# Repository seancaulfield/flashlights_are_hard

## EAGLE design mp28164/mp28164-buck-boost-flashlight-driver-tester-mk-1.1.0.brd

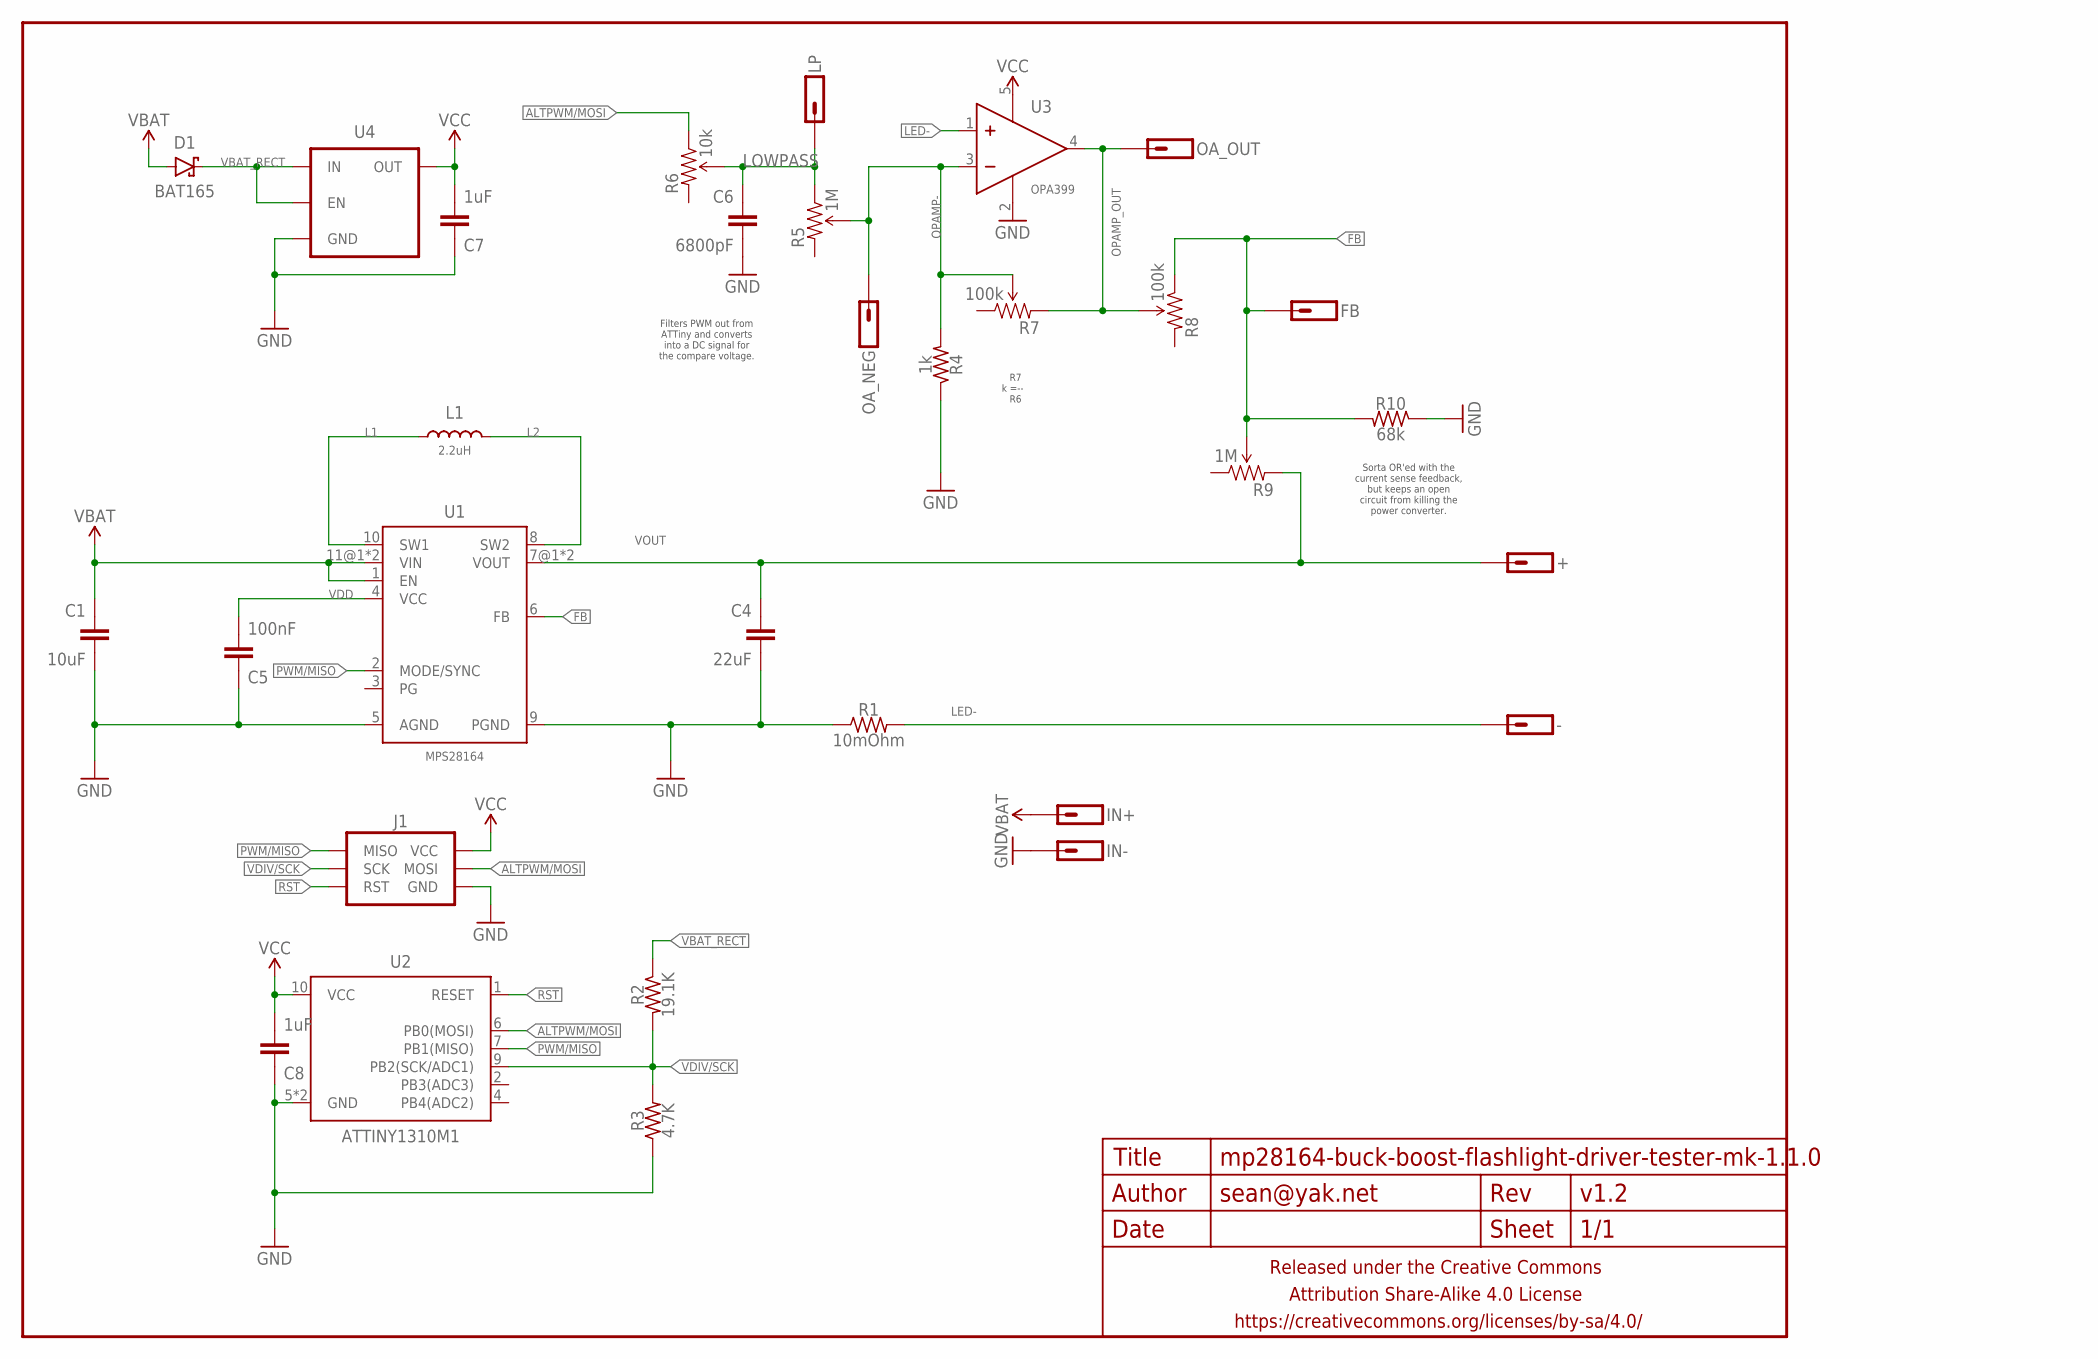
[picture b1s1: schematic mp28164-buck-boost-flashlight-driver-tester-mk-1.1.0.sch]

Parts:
+: M01PTH-1MM-CIR-NS; 1X01-1MM-CIR-NS
-: M01PTH-1MM-CIR-NS; 1X01-1MM-CIR-NS
C1: 10uF; C1206
C4: 22uF; C1206
C5: 100nF; C0402
C6: 6800pF; C0402
C7, C8: 1uF; C0402
D1: BAT165; SOD323-SCHOTTKY
FB: M01SMD-1MM-DIA-NS; 1X01-SMD-1MM-DIA-NS
FRAME1: FRAME-LETTERNO_PACKAGE; DUMMY
IN+: M01PTH-1MM-CIR-NS; 1X01-1MM-CIR-NS
IN-: M01PTH-1MM-CIR-NS; 1X01-1MM-CIR-NS
J1: AVR_SPI_PRG_6PTH; 2X3
L1: 2.2uH; XAL7070
LP: M01SMD-1MM-DIA-NS; 1X01-SMD-1MM-DIA-NS
OA_NEG: M01SMD-1MM-DIA-NS; 1X01-SMD-1MM-DIA-NS
OA_OUT: M01SMD-1MM-DIA-NS; 1X01-SMD-1MM-DIA-NS
R1: 10mOhm; R1206
R2: 19.1K; R0402
R3: 4.7K; R0402
R4: 1k; R0402
R5, R9: 1M; EVM3Y-LESS
R6: 10k; EVM3Y-LESS
R7, R8: 100k; EVM3Y-LESS
R10: 68k; R0402
U1: MPS28164
U2: ATTINY1310M1; QFN10(2X5)
U3: OPA399; SC70
U4: V_REG_ENTLV700; SC70

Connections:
ALTPWM/MOSI: J1.4 (MOSI), R6.A (CCW), U2.6 (PB0(MOSI))
FB: FB.P$1, R8.A (CCW), R9.S (WIPER), R10.2, U1.6 (FB)
GND: C1.2, C4.2, C5.1, C6.2, C7.1, C8.1, IN-.1, J1.6 (GND), R1.1, R3.1, R4.1, R10.1, U1.5 (AGND), U1.9 (PGND), U2.5 (GND), U2.PAD (GND), U3.2 (V-), U4.2 (GND)
L1: L1.P$1 (1), U1.10 (SW1)
L2: L1.P$2 (2), U1.8 (SW2)
LED-: -.1, R1.2, U3.1 (IN+)
LOWPASS: C6.1, LP.P$1, R5.A (CCW), R6.S (WIPER)
OPAMP-: OA_NEG.P$1, R4.2, R5.S (WIPER), R7.S (WIPER), U3.3 (IN-)
OPAMP_OUT: OA_OUT.P$1, R7.E (CW), R8.S (WIPER), U3.4 (OUT)
PWM/MISO: J1.1 (MISO), U1.2 (MODE/SYNC), U2.7 (PB1(MISO))
RST: J1.5 (RST), U2.1 (RESET)
VBAT: C1.1, D1.A, IN+.1, U1.1 (EN), U1.11@1 (VIN), U1.11@2 (VIN)
VBAT_RECT: D1.C, R2.1, U4.1 (IN), U4.3 (EN)
VCC: C7.2, C8.2, J1.2 (VCC), U2.10 (VCC), U3.5 (V+), U4.5 (OUT)
VDD: C5.2, U1.4 (VCC)
VDIV/SCK: J1.3 (SCK), R2.2, R3.2, U2.9 (PB2(SCK/ADC1))
VOUT: +.1, C4.1, R9.E (CW), U1.7@1 (VOUT), U1.7@2 (VOUT)

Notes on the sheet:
Filters PWM out from ATTiny and converts into a DC signal for the compare voltage.
R7 k =-- R6
Sorta OR'ed with the current sense feedback, but keeps an open circuit from killing the power converter.

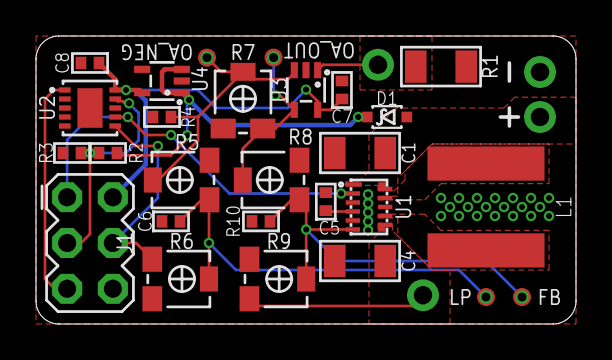
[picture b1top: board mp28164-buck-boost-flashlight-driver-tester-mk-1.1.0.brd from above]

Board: 2 copper layers, 30.0 x 16.0 mm, 32 parts (0 on the bottom side), 17 nets.

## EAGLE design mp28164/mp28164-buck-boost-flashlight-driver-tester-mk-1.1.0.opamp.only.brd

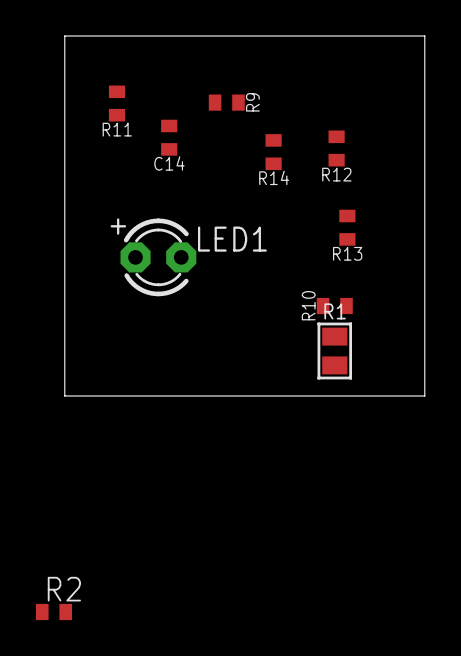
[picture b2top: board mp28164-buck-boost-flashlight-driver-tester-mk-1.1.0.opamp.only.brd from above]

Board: 2 copper layers, 20.0 x 20.0 mm, 10 parts (0 on the bottom side), 7 nets, no tracks yet.

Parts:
C14: 0.000001; C0402
LED1: LED3MM
R1: .01; R0805-TIGHTER
R2: 91000; R0402
R9, R10: 10000; R0402
R11: 150000; R0402
R12: 47000; R0402
R13: 750000; R0402
R14: 360000; R0402

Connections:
GND: C14.2, R1.1, R10.2, R11.1
LED-: LED1.K, R1.2
LOWPASS: C14.1, R9.1, R14.2
MIX1: R11.2, R12.1, R13.1
OPAMP-: R2.2, R10.1
OPAMP_OUT: R2.1, R12.2
VCC: LED1.A, R13.2

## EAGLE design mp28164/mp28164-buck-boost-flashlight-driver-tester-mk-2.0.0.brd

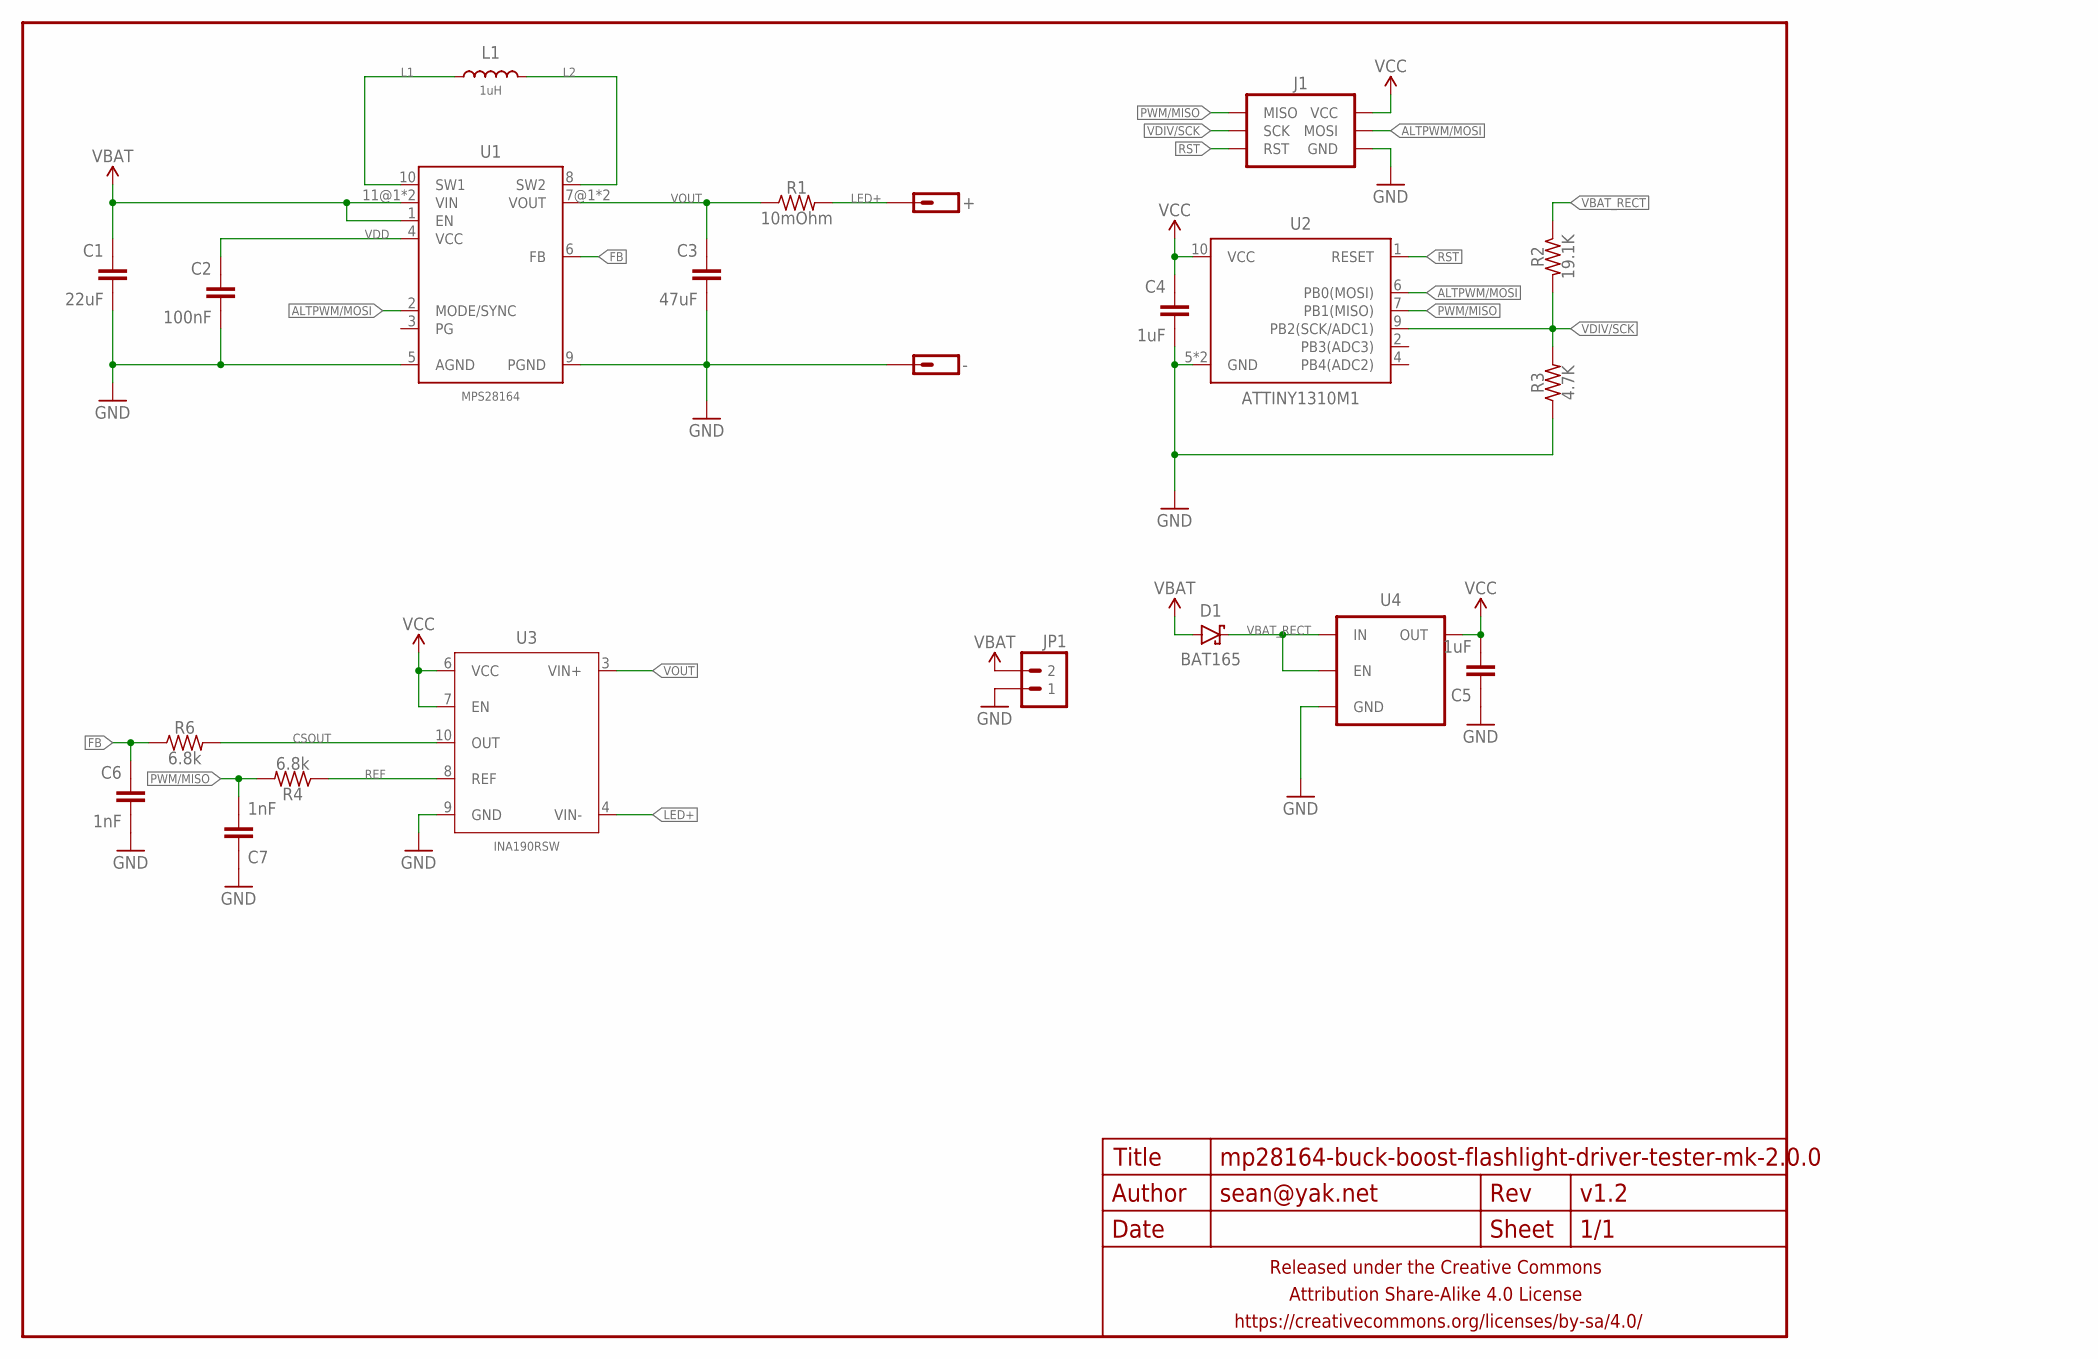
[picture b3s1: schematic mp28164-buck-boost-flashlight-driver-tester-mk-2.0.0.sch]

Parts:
+: M01PTH-1.2MM-NS; 1X01-1.2MM-NS
-: M01PTH-1.2MM-NS; 1X01-1.2MM-NS
C1: 22uF; C1206
C2: 100nF; C0402
C3: 47uF; C1206
C4, C5: 1uF; C0402
C6, C7: 1nF; C0402
D1: BAT165; SOD323-SCHOTTKY
FRAME1: FRAME-LETTERNO_PACKAGE; DUMMY
J1: AVR_SPI_PRG_6PTH; 2X3
JP1: M02PTH; 1X02
L1: 1uH; XAL60XX
R1: 10mOhm; R1206
R2: 19.1K; R0402
R3: 4.7K; R0402
R4, R6: 6.8k; R0402
U1: MPS28164
U2: ATTINY1310M1; QFN10(2X5)
U3: INA190RSW; UQFN-10
U4: V_REG_ENTLV700; SC70

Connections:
ALTPWM/MOSI: J1.4 (MOSI), U1.2 (MODE/SYNC), U2.6 (PB0(MOSI))
CSOUT: R6.2, U3.10 (OUT)
FB: C6.1, R6.1, U1.6 (FB)
GND: -.P$1, C1.2, C2.2, C3.2, C4.2, C5.1, C6.2, C7.1, J1.6 (GND), JP1.1, R3.1, U1.5 (AGND), U1.9 (PGND), U2.5 (GND), U2.PAD (GND), U3.9 (GND), U4.2 (GND)
L1: L1.P$1 (1), U1.10 (SW1)
L2: L1.P$2 (2), U1.8 (SW2)
LED+: +.P$1, R1.2, U3.4 (VIN-)
PWM/MISO: C7.2, J1.1 (MISO), R4.2, U2.7 (PB1(MISO))
REF: R4.1, U3.8 (REF)
RST: J1.5 (RST), U2.1 (RESET)
VBAT: C1.1, D1.A, JP1.2, U1.1 (EN), U1.11@1 (VIN), U1.11@2 (VIN)
VBAT_RECT: D1.C, R2.1, U4.1 (IN), U4.3 (EN)
VCC: C4.1, C5.2, J1.2 (VCC), U2.10 (VCC), U3.6 (VCC), U3.7 (EN), U4.5 (OUT)
VDD: C2.1, U1.4 (VCC)
VDIV/SCK: J1.3 (SCK), R2.2, R3.2, U2.9 (PB2(SCK/ADC1))
VOUT: C3.1, R1.1, U1.7@1 (VOUT), U1.7@2 (VOUT), U3.3 (VIN+)

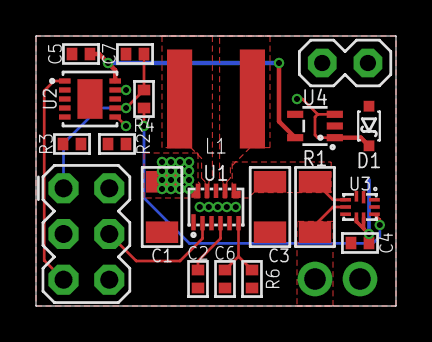
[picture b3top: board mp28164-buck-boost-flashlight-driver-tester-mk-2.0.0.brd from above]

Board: 2 copper layers, 20.0 x 15.0 mm, 23 parts (0 on the bottom side), 16 nets.

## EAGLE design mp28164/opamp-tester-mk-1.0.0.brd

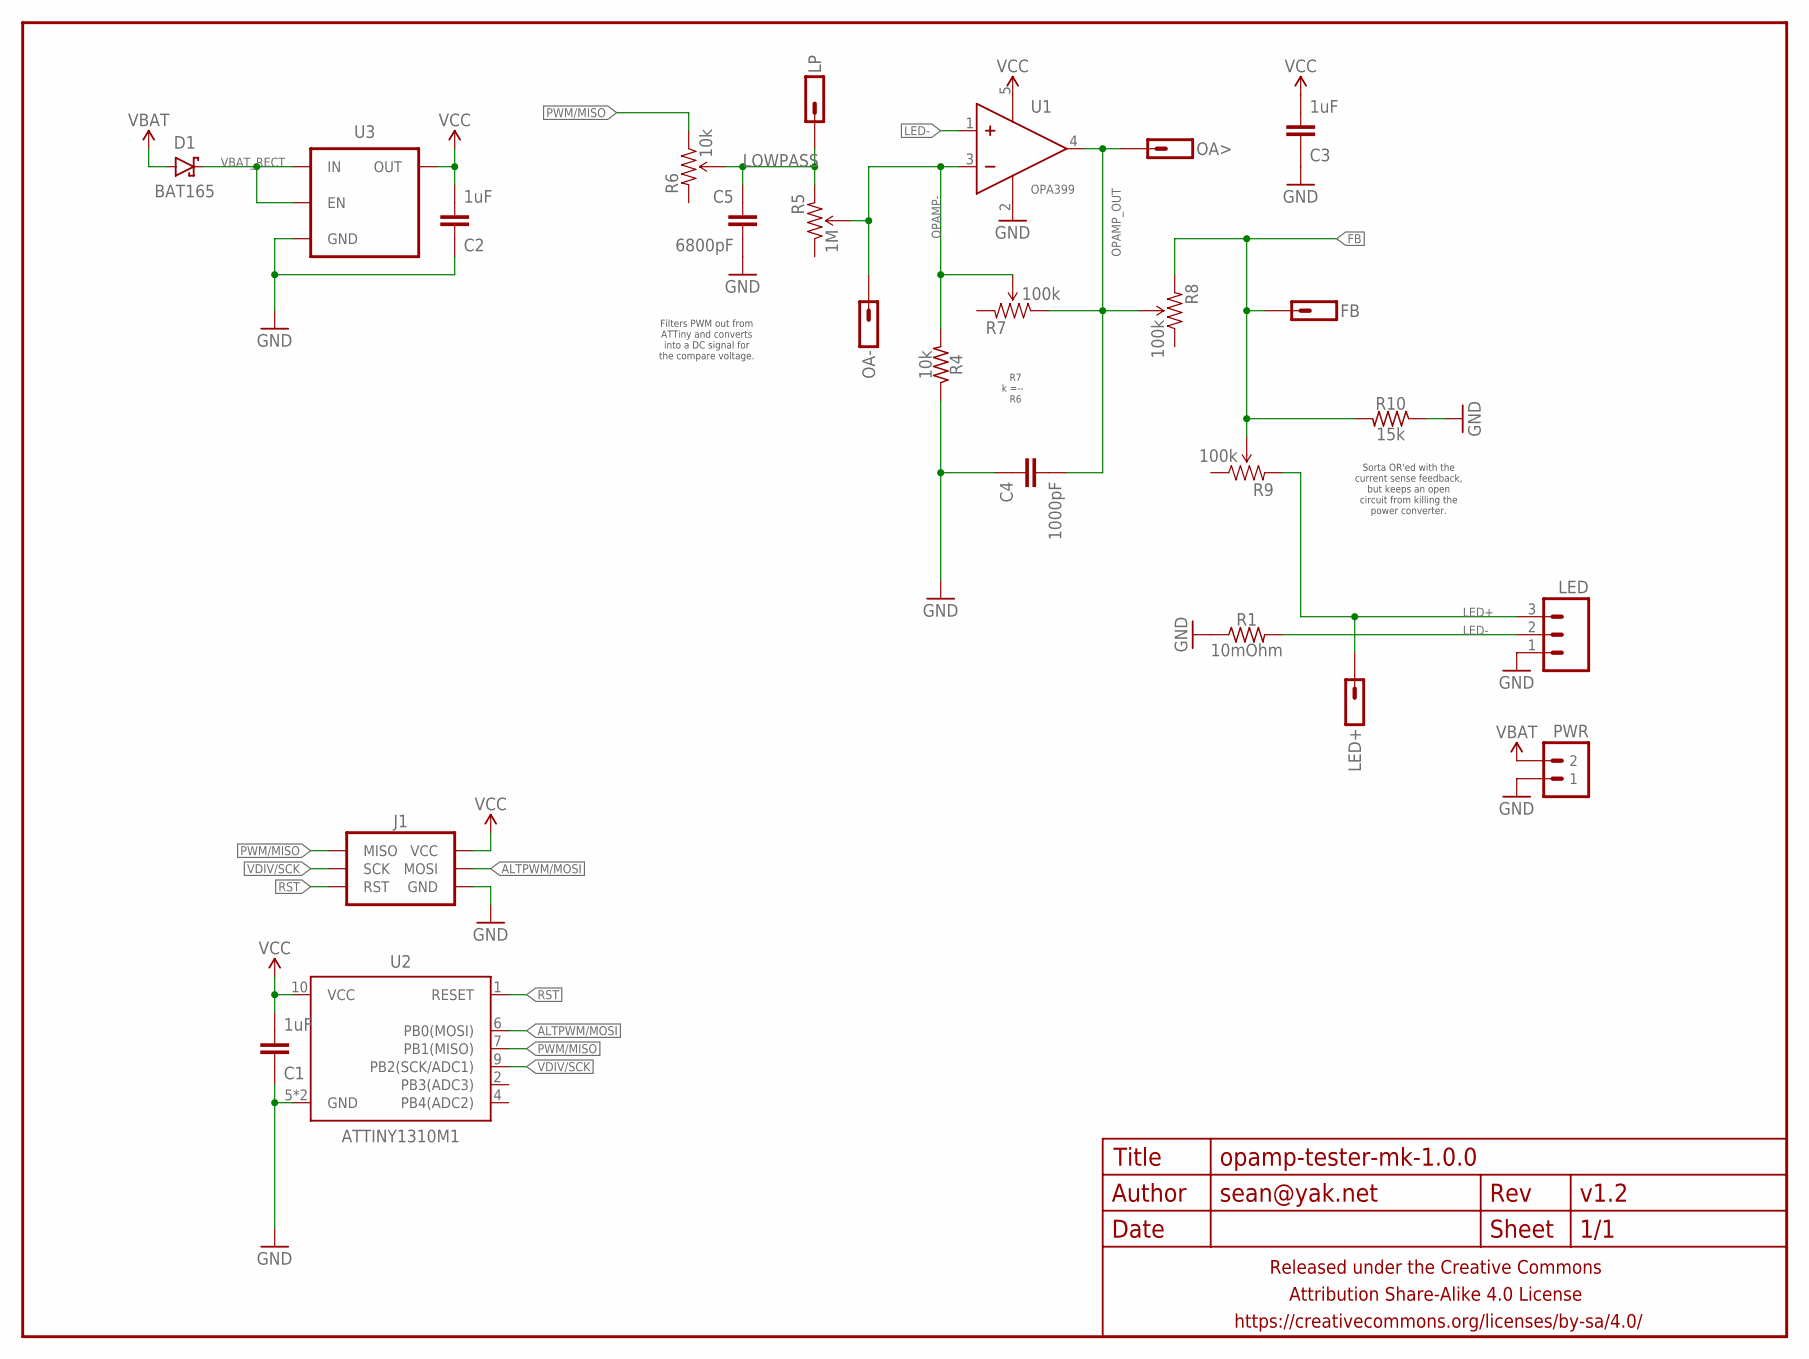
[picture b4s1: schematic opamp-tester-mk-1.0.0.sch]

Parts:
C1, C2, C3: 1uF; C0402
C4: 1000pF; C0402
C5: 6800pF; C0402
D1: BAT165; SOD323-SCHOTTKY
FB: M01PTH-0.7MM-CIR; 1X01-0.7MM-CIR
FRAME1: FRAME-LETTERNO_PACKAGE; DUMMY
J1: AVR_SPI_PRG_6SMD_TEST_POINTS; 2X3_SMD_TEST_POINTS
LED: M03SCREW; SCREWTERMINAL-3.5MM-3
LED+: M01PTH-0.7MM-CIR; 1X01-0.7MM-CIR
LP: M01PTH-0.7MM-CIR; 1X01-0.7MM-CIR
OA-: M01PTH-0.7MM-CIR; 1X01-0.7MM-CIR
OA>: M01PTH-0.7MM-CIR; 1X01-0.7MM-CIR
PWR: M02PTH-2MM; 1X02-2MM-PTH
R1: 10mOhm; R1206
R4: 10k; R0402
R5: 1M; EVM3Y-LESS
R6: 10k; EVM3Y-LESS
R7, R8, R9: 100k; EVM3Y-LESS
R10: 15k; R0402
U1: OPA399; SC70
U2: ATTINY1310M1; QFN10(2X5)
U3: V_REG_ENTLV700; SC70

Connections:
ALTPWM/MOSI: J1.4 (MOSI), U2.6 (PB0(MOSI))
FB: FB.P$1, R8.E (CW), R9.S (WIPER), R10.2
GND: C1.1, C2.1, C3.1, C4.1, C5.2, J1.6 (GND), LED.1, PWR.P$1 (1), R1.1, R4.1, R10.1, U1.2 (V-), U2.5 (GND), U2.PAD (GND), U3.2 (GND)
LED+: LED.3, LED+.P$1, R9.E (CW)
LED-: LED.2, R1.2, U1.1 (IN+)
LOWPASS: C5.1, LP.P$1, R5.E (CW), R6.S (WIPER)
OPAMP-: OA-.P$1, R4.2, R5.S (WIPER), R7.S (WIPER), U1.3 (IN-)
OPAMP_OUT: C4.2, OA>.P$1, R7.A (CCW), R8.S (WIPER), U1.4 (OUT)
PWM/MISO: J1.1 (MISO), R6.A (CCW), U2.7 (PB1(MISO))
RST: J1.5 (RST), U2.1 (RESET)
VBAT: D1.A, PWR.P$2 (2)
VBAT_RECT: D1.C, U3.1 (IN), U3.3 (EN)
VCC: C1.2, C2.2, C3.2, J1.2 (VCC), U1.5 (V+), U2.10 (VCC), U3.5 (OUT)
VDIV/SCK: J1.3 (SCK), U2.9 (PB2(SCK/ADC1))

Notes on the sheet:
Filters PWM out from ATTiny and converts into a DC signal for the compare voltage.
R7 k =-- R6
Sorta OR'ed with the current sense feedback, but keeps an open circuit from killing the power converter.

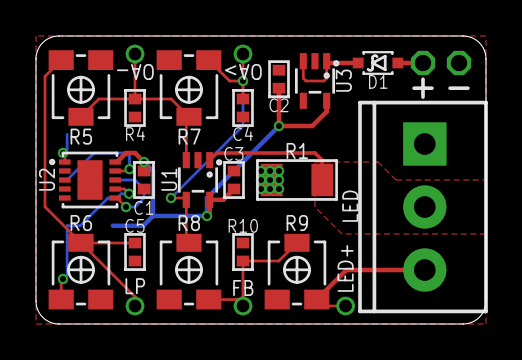
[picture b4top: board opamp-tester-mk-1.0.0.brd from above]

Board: 2 copper layers, 25.0 x 16.0 mm, 26 parts (1 on the bottom side), 14 nets.

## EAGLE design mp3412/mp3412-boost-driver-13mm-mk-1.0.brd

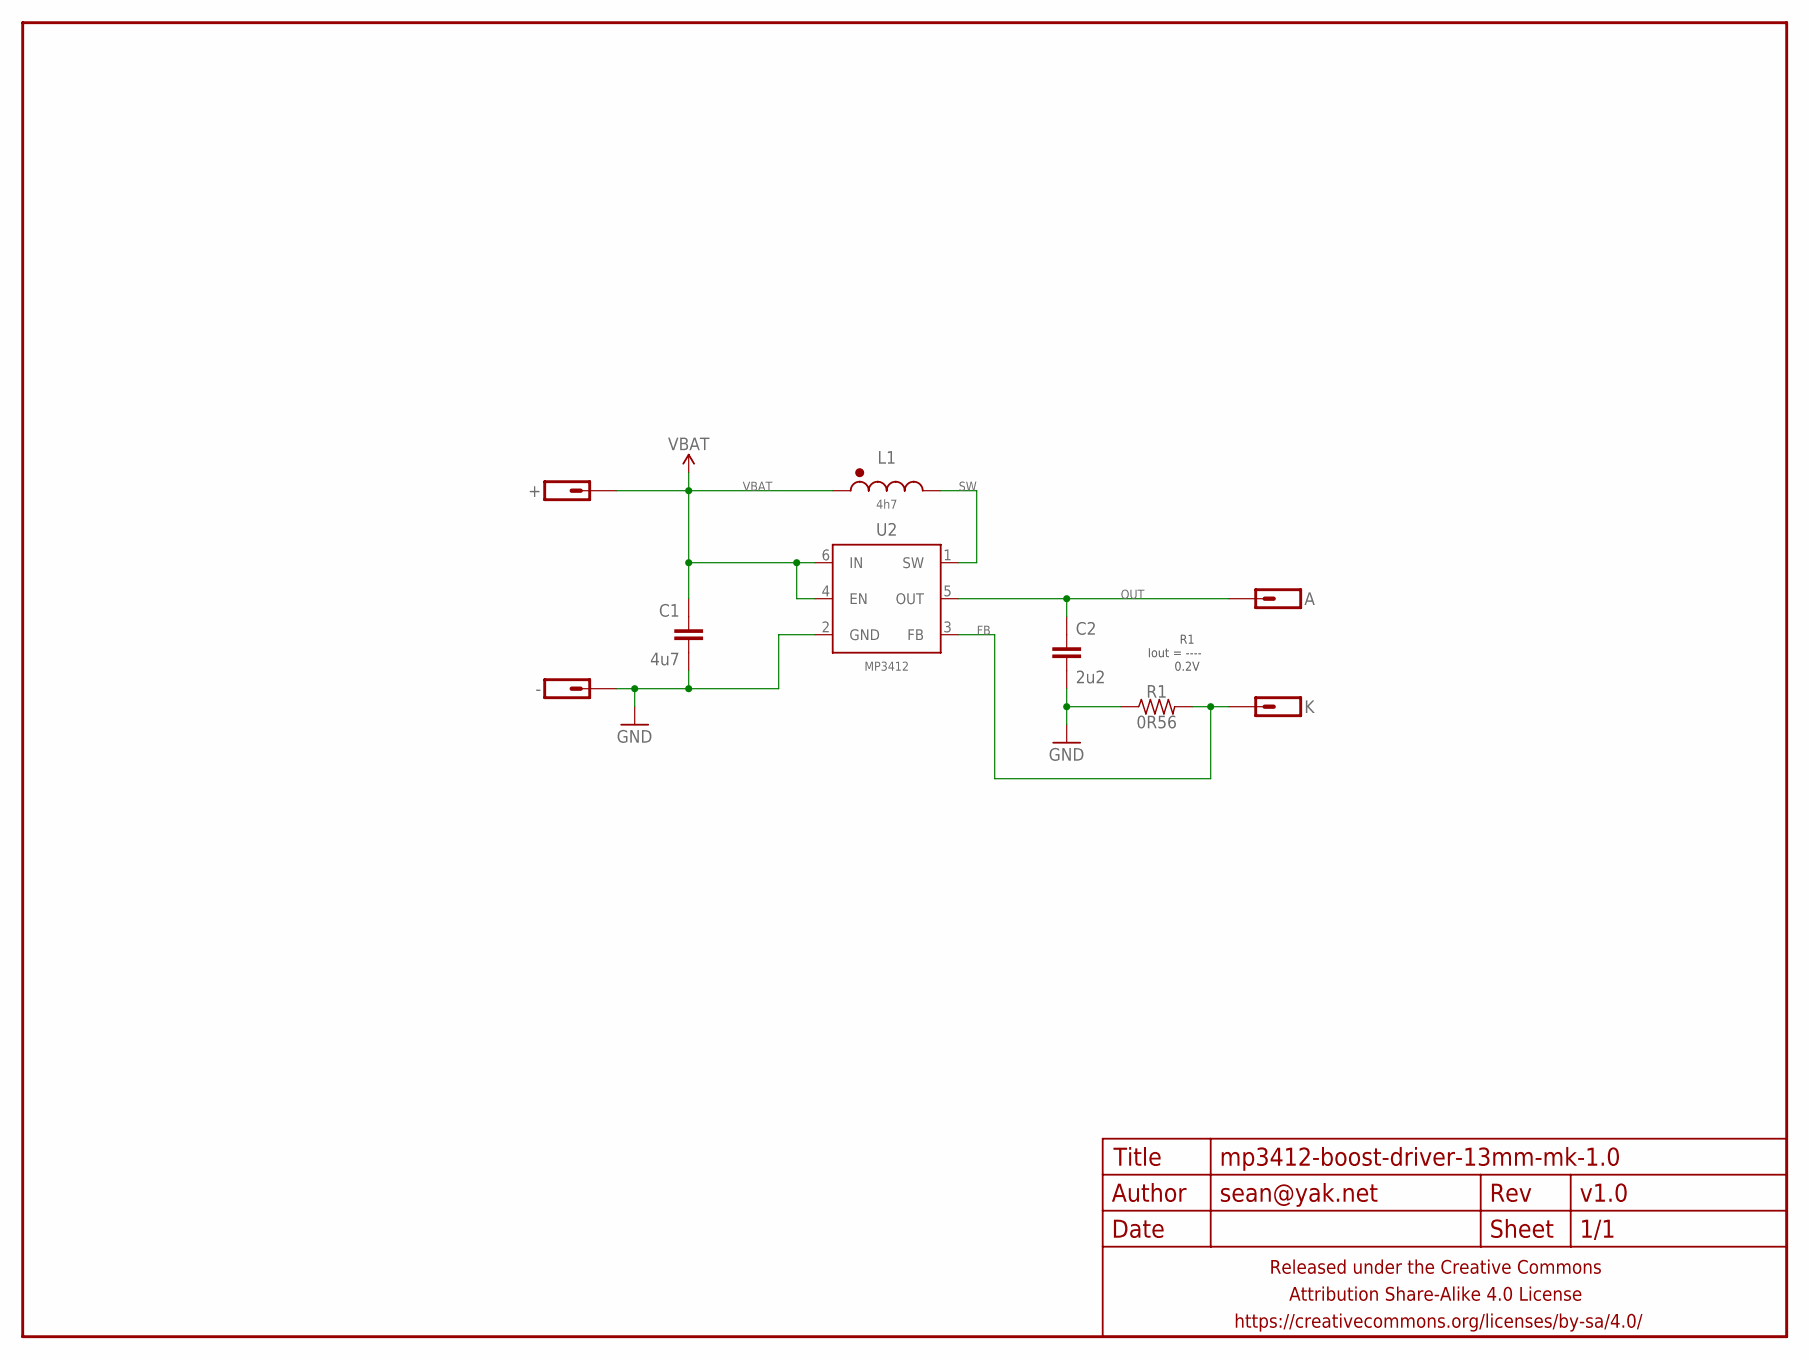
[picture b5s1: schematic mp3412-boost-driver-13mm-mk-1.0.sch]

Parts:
+: M01NOT-A-VIA-NOPE; 1X01_NOSILK_NOSTOP
-: M01NOT-A-VIA-NOPE; 1X01_NOSILK_NOSTOP
A: M01SMD_1.5X2MM; 1X01_1.5X2MM
C1: 4u7; C0603-TIGHTER
C2: 2u2; C0603-TIGHTER
FRAME1: FRAME-LETTERNO_PACKAGE; DUMMY
K: M01SMD_1.5X2MM; 1X01_1.5X2MM
L1: 4h7; EPL2014
R1: 0R56; R0603-TIGHTER
U2: MP3412; TSOT-23-6

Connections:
FB: K.P$1, R1.2, U2.3 (FB)
GND: -.P$1, C1.2, C2.2, R1.1, U2.2 (GND)
OUT: A.P$1, C2.1, U2.5 (OUT)
SW: L1.P$2 (2), U2.1 (SW)
VBAT: +.P$1, C1.1, L1.P$1 (1), U2.4 (EN), U2.6 (IN)

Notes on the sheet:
R1 Iout = ---- 0.2V

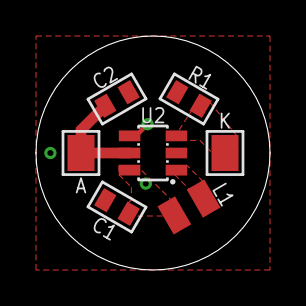
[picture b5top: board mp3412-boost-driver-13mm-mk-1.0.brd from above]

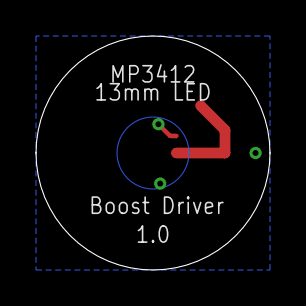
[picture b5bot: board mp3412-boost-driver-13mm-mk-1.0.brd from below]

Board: 2 copper layers, 13.0 x 13.0 mm, 10 parts (2 on the bottom side), 5 nets.

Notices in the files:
parts and their libraries:
a_parts: Released under the Creative Commons Attribution Share-Alike 4.0 License
a_parts: https://creativecommons.org/licenses/by-sa/4.0
a_parts: Released under the Creative Commons
